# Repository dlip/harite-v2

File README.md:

# Harite v2 Directional keyboard

All the features of [Harite v1](https://github.com/dlip/harite) plus:

- A modular thumb cluster which allows for various devices including thumbsticks, trackballs, trackpads and extra 5 way switches
- 1/4-20 camera mount compatible nuts for flexible tenting orientations
- 3D models created using FreeCAD to avoid proprietary software use

To make your own, follow the [build guide](./build.md)

## Gallery

[Typing video](https://youtu.be/VckVijPMjfQ)

[YouTube video of playing Doom with Harite v2](https://youtu.be/kz_-oAf_KqY)

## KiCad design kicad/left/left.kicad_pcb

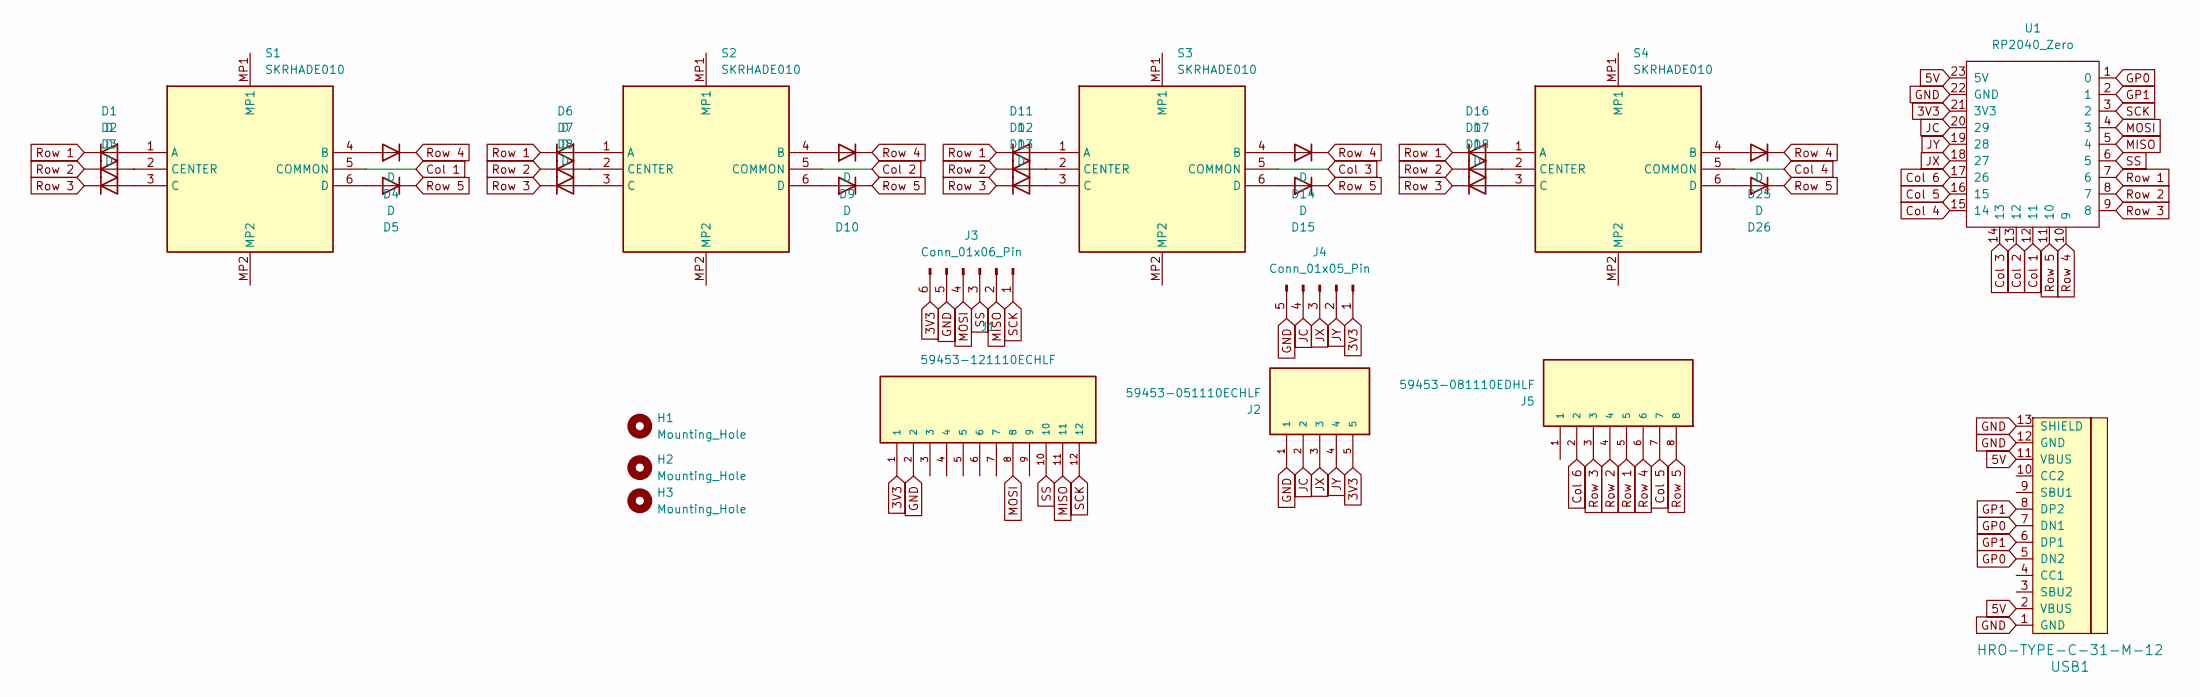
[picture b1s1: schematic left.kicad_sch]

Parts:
D1, D2, D3, D4, D5, D6, D7, D8, D9, D10, D11, D12, D13, D14, D15, D16, D17, D18, D25, D26: D; Diode_SOD-123
H1, H2, H3: Mounting_Hole; MountingHole_2.2mm_M2_Pad_Via
J1: 59453-121110ECHLF; AMPHENOL_59453-121110ECHLF; PARTREV A
J2: 59453-051110ECHLF; AMPHENOL_59453-051110ECHLF; PARTREV A
J3: Conn_01x06_Pin; Pointing-connector
J4: Conn_01x05_Pin; Joystick-connector
J5: 59453-081110EDHLF; AMPHENOL_59453-081110EDHLF; PARTREV D
S1, S2, S3, S4: SKRHADE010; Manufacturer_Part_Number SKRHADE010; Mouser Part Number 688-SKRHAD
U1: RP2040_Zero
USB1: HRO-TYPE-C-31-M-12

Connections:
3V3: J1.1, J2.5, J3.6, J4.1, U1.21 (3V3)
5V: U1.23 (5V), USB1.2 (VBUS), USB1.11 (VBUS)
Col 1: S1.5 (COMMON), U1.12 (11)
Col 2: S2.5 (COMMON), U1.13 (12)
Col 3: S3.5 (COMMON), U1.14 (13)
Col 4: S4.5 (COMMON), U1.15 (14)
Col 5: J5.7, U1.16 (15)
Col 6: J5.2, U1.17 (26)
GND: J1.2, J2.1, J3.5, J4.5, U1.22 (GND), USB1.1 (GND), USB1.12 (GND), USB1.13 (SHIELD)
GP0: U1.1 (0), USB1.5 (DN2), USB1.7 (DN1)
GP1: U1.2 (1), USB1.6 (DP1), USB1.8 (DP2)
JC: J2.2, J4.4, U1.20 (29)
JX: J2.3, J4.3, U1.18 (27)
JY: J2.4, J4.2, U1.19 (28)
MISO: J1.11, J3.2, U1.5 (4)
MOSI: J1.8, J3.4, U1.4 (3)
unnamed: D1.2 (A), S1.1 (A)
unnamed: D2.2 (A), S1.2 (CENTER)
unnamed: D3.2 (A), S1.3 (C)
unnamed: D4.2 (A), S1.4 (B)
unnamed: D5.2 (A), S1.6 (D)
unnamed: D6.2 (A), S2.1 (A)
unnamed: D7.2 (A), S2.2 (CENTER)
unnamed: D8.2 (A), S2.3 (C)
unnamed: D9.2 (A), S2.4 (B)
unnamed: D10.2 (A), S2.6 (D)
unnamed: D11.2 (A), S3.1 (A)
unnamed: D12.2 (A), S3.2 (CENTER)
unnamed: D13.2 (A), S3.3 (C)
unnamed: D14.2 (A), S3.4 (B)
unnamed: D15.2 (A), S3.6 (D)
unnamed: D16.2 (A), S4.1 (A)
unnamed: D17.2 (A), S4.2 (CENTER)
unnamed: D18.2 (A), S4.3 (C)
unnamed: D25.2 (A), S4.4 (B)
unnamed: D26.2 (A), S4.6 (D)
Row 1: D1.1 (K), D6.1 (K), D11.1 (K), D16.1 (K), J5.5, U1.7 (6)
Row 2: D2.1 (K), D7.1 (K), D12.1 (K), D17.1 (K), J5.4, U1.8 (7)
Row 3: D3.1 (K), D8.1 (K), D13.1 (K), D18.1 (K), J5.3, U1.9 (8)
Row 4: D4.1 (K), D9.1 (K), D14.1 (K), D25.1 (K), J5.6, U1.10 (9)
Row 5: D5.1 (K), D10.1 (K), D15.1 (K), D26.1 (K), J5.8, U1.11 (10)
SCK: J1.12, J3.1, U1.3 (2)
SS: J1.10, J3.3, U1.6 (5)

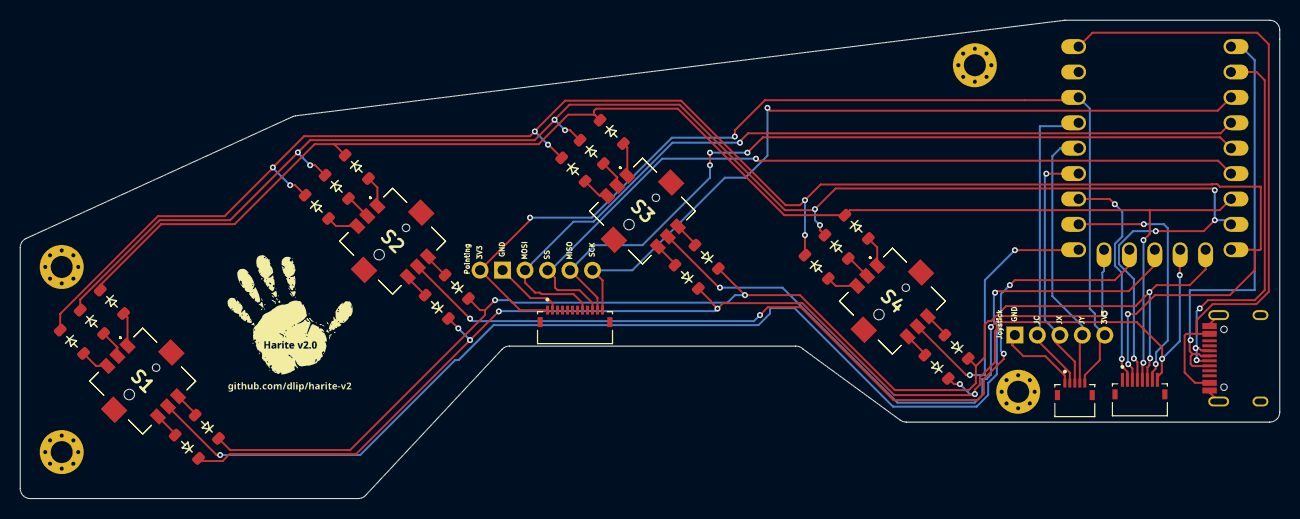
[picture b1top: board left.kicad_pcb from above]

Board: 2 copper layers, 126.0 x 47.8 mm, 35 parts (0 on the bottom side), 43 nets.

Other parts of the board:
H4: Mounting_Hole; MountingHole_2.2mm_M2_Pad_Via

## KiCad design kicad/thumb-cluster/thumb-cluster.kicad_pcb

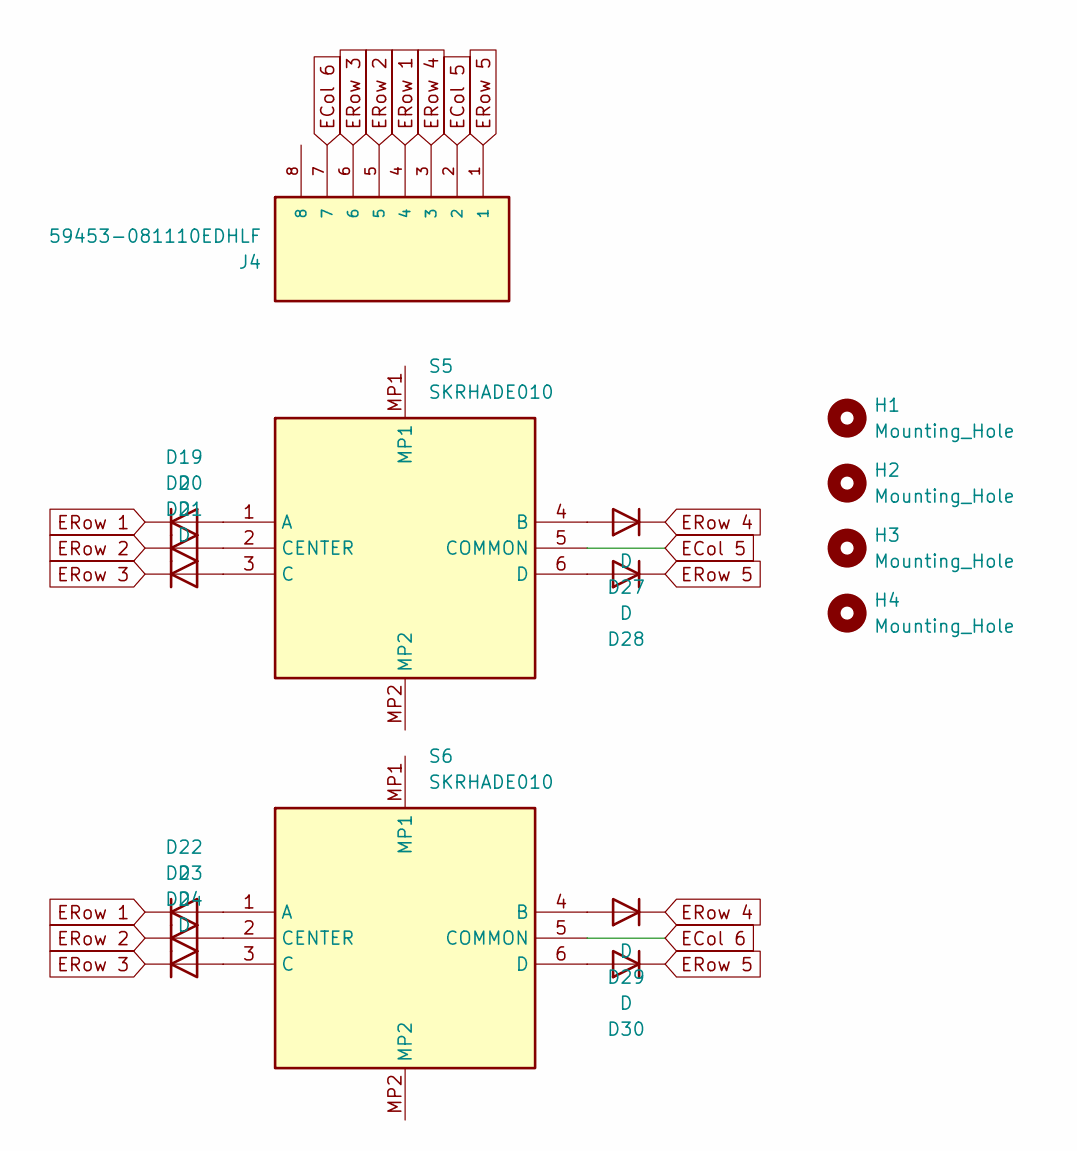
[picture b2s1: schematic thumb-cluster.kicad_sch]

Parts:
D19, D20, D21, D22, D23, D24, D27, D28, D29, D30: D; Diode_SOD-123
H1, H2, H3, H4: Mounting_Hole; MountingHole_2.2mm_M2_Pad_Via
J4: 59453-081110EDHLF; AMPHENOL_59453-081110EDHLF; PARTREV D
S5, S6: SKRHADE010; Manufacturer_Part_Number SKRHADE010; Mouser Part Number 688-SKRHAD

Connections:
ECol 5: J4.2, S5.5 (COMMON)
ECol 6: J4.7, S6.5 (COMMON)
ERow 1: D19.1 (K), D22.1 (K), J4.4
ERow 2: D20.1 (K), D23.1 (K), J4.5
ERow 3: D21.1 (K), D24.1 (K), J4.6
ERow 4: D27.1 (K), D29.1 (K), J4.3
ERow 5: D28.1 (K), D30.1 (K), J4.1
unnamed: D19.2 (A), S5.1 (A)
unnamed: D20.2 (A), S5.2 (CENTER)
unnamed: D21.2 (A), S5.3 (C)
unnamed: D22.2 (A), S6.1 (A)
unnamed: D23.2 (A), S6.2 (CENTER)
unnamed: D24.2 (A), S6.3 (C)
unnamed: D27.2 (A), S5.4 (B)
unnamed: D28.2 (A), S5.6 (D)
unnamed: D29.2 (A), S6.4 (B)
unnamed: D30.2 (A), S6.6 (D)

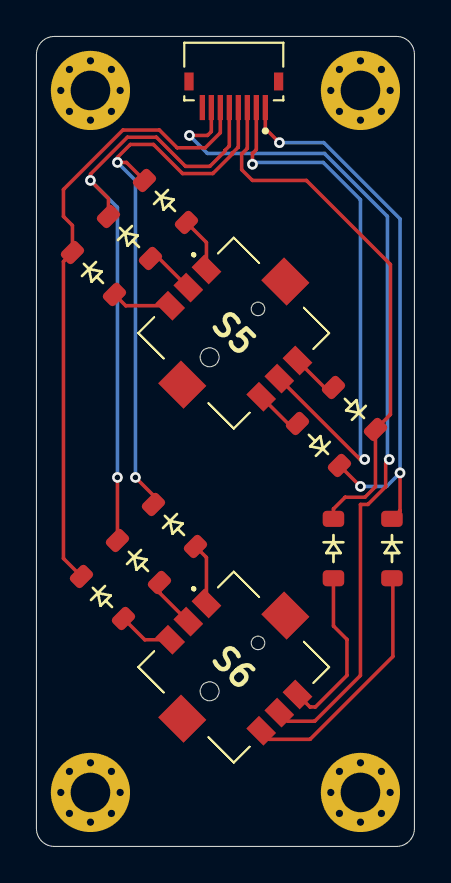
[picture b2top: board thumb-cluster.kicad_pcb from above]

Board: 2 copper layers, 21.0 x 45.0 mm, 17 parts (0 on the bottom side), 17 nets.

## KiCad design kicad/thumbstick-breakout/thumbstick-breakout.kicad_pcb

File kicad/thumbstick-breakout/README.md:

Adapted from https://github.com/dbenoy/thumbstick-breakout to include a FPC connector

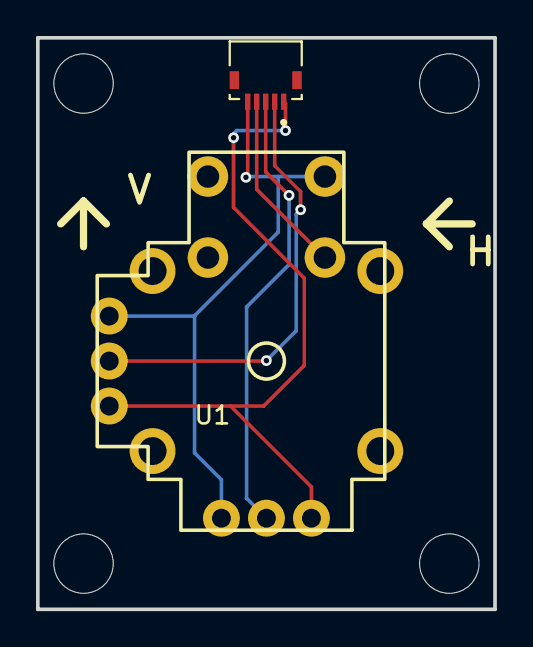
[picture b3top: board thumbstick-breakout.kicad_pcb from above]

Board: 2 copper layers, 25.4 x 31.8 mm, 6 parts (0 on the bottom side), 5 nets.

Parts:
J1: 59453-051110ECHLF; AMPHENOL_59453-051110ECHLF
U1: Joystick
U$3, U$4, U$5, U$6: Screw Hole

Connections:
/HORZ: J1.3, U1.2 (H)
/SEL: J1.4, U1.a (SEL+)
/VERT: J1.2, U1.2' (V)
GND: J1.5, U1.1 (H-), U1.1' (V-), U1.c (SEL-)
VCC: J1.1, U1.3 (H+), U1.3' (V+)

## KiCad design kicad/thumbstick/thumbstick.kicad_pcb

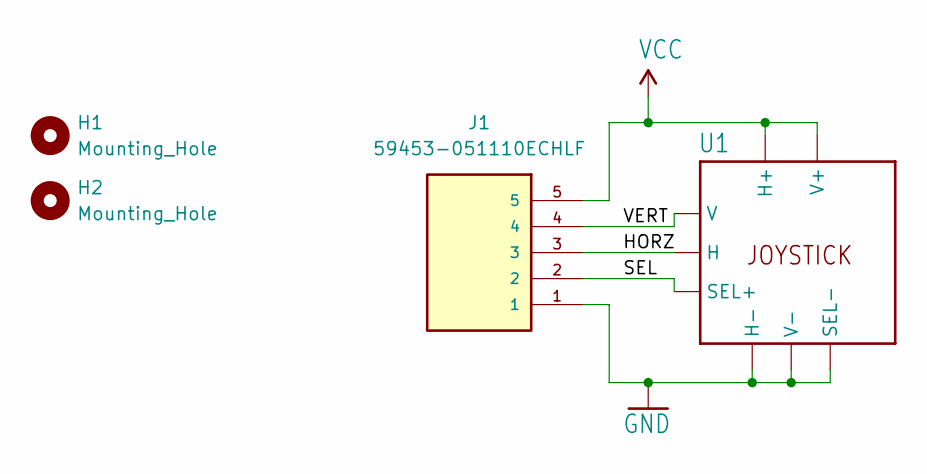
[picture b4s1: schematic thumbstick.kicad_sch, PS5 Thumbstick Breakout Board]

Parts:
H1, H2: Mounting_Hole; MountingHole_2.2mm_M2_Pad_Via
J1: 59453-051110ECHLF; AMPHENOL_59453-051110ECHLF; PARTREV A
U1: Joystick

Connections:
/HORZ: J1.3, U1.2 (H)
/SEL: J1.2, U1.a (SEL+)
/VERT: J1.4, U1.2' (V)
GND: J1.1, U1.1 (H-), U1.1' (V-), U1.c (SEL-)
VCC: J1.5, U1.3 (H+), U1.3' (V+)

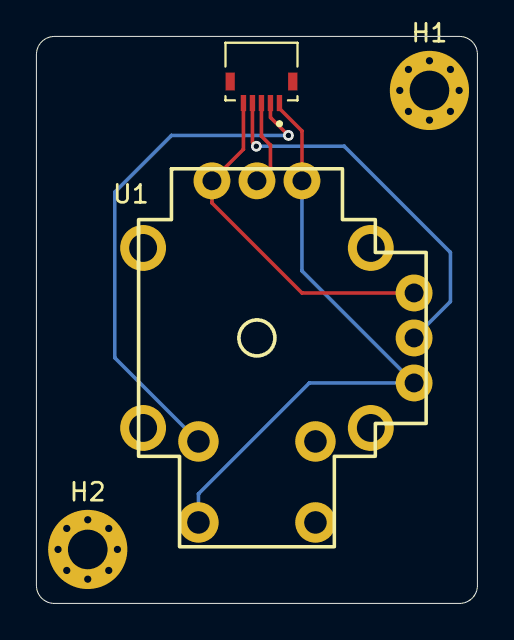
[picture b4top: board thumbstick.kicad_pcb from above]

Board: 2 copper layers, 24.5 x 31.5 mm, 4 parts (0 on the bottom side), 5 nets.

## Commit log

2024-11-28 Add project
2024-11-28 move kicad
2024-11-28 basic schematic
2024-11-29 Add 5034800540 and 5034801000
2024-11-29 Fix model
2024-11-29 fix orientation
2024-11-30 Switch back to rp2040 zero
2024-12-01 add joycon
2024-12-01 move diodes
2024-12-03 Change to ps5 joystick
2024-12-03 fix footprints
2024-12-03 Update nets
2024-12-03 routing
2024-12-04 break up parts
2024-12-04 wiring
2024-12-05 Freecad xring
2024-12-06 Freecad pcb
2024-12-08 Create base
2024-12-08 Add thumb cluster
2024-12-11 Add connectors
2024-12-11 Rename caps
2024-12-11 Update footprints
2024-12-11 reimport files
2024-12-11 Add joystick breakout
2024-12-11 update freecad
2024-12-12 extend breakout
2024-12-12 Add stem
2024-12-12 Add tent
2024-12-12 update thumb cluster
2024-12-14 tented
2024-12-14 tent
2024-12-14 Add holes
2024-12-14 holes
2024-12-14 Add vertical case
2024-12-14 vertical
2024-12-15 thumb pos
2024-12-15 thumb
2024-12-15 thumb 2
2024-12-15 trackball holder
2024-12-16 thumb 3
2024-12-18 Use only fcc on thumbstick
2024-12-18 Update thumbstick
2024-12-18 Add right
2024-12-18 place right components
2024-12-18 wire right
2024-12-19 Add gerbers
2024-12-19 Add tindie
2024-12-19 Add bom and camera mount
2024-12-19 Another case
2024-12-20 simple case
2024-12-20 assembly
2024-12-20 Base with top
2024-12-21 top and bottom
2024-12-21 case
2024-12-21 add thumbstick
2024-12-22 rotate
2024-12-23 base
2024-12-23 contained thumbstick
2024-12-24 tall box
2024-12-24 print
2024-12-28 trackball
2024-12-30 fix errors
2024-12-30 chamfer
2024-12-31 filet
2024-12-31 mount
2024-12-31 thicken
2024-12-31 thumbstick
2025-01-01 increase thumb cluster tolerance
2025-01-01 cirque
2025-01-02 horizontal mount
2025-01-02 horizontal trackball
2025-01-03 cleanup
2025-01-03 add support
2025-01-03 thicken mount connection
2025-01-03 fix top
2025-01-03 flatten mount
2025-01-07 Add caps
2025-01-09 Change mount
2025-01-10 Improve mount
2025-01-10 Add stls
2025-01-11 Readme
2025-01-11 Add parts
2025-01-11 Add models
2025-01-11 Add build guide
2025-01-11 Add firmware link
2025-01-11 Add doom video
2025-01-11 Change to link
2025-01-12 Add right casetop
2025-01-14 Add Kettlebell desktop mode
2025-01-14 Update pic
2025-01-16 Add cirque thumb cluster
2025-01-17 Add Horizontal configuration
2025-02-07 controller case
2025-05-15 Update links
2025-05-15 Update firmware links
2025-05-21 Add typing video
2025-06-23 Add vial keymap link

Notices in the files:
kicad/thumbstick-breakout/thumbstick-breakout.kicad_pcb:
https://creativecommons.org/licenses/by-sa/4.0
This hardware is licensed under Creative Commons ShareAlike 4.0 International
